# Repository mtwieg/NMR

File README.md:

NMR
===

Welcome to the Open Source Mobile NMR Relaxometry Platform repository on github.

You can download the entire repository without needing to install or register with github. To do so, go to the repository homepage and click the ZIP icon on the upper toolbar.

After presenting this project at ISMRM 2013, I received several questions about the future direction for the platform. At the moment there are numerous possible improvements to the hardware:

1. Further minitiarization (we estimate the platform could be shrunk by a factor of three or so without compromise).

2. Wider frequency range (for very low field work)

3. Addition of gradient amplifiers (imaging)

4. Greater processing power, for standalone data processing.

Such improvements should be driven by the intended applications of the platform, and at this time we have not settled on any applications to explore.  Until we decide what sort of applications are worth pursuing, we will probably hold off on any major hardware revisions.

We are, of course, open to any and all suggestions.

Mike Twieg
mdt24@case.edu

## Licensing

- content in `/BOMs` and `/EAGLE` is licensed under [CERN OHL P v2.0](LICENSES/CERN-OHL-P-2.0)
- content in `/BOMs` and `/EAGLE` is licensed under [MIT](LICENSES/MIT)
- content in `/BOMs` and `/EAGLE` is licensed under [CC BY 4.0](LICENSES/CC-BY-4.0)

See [.reuse/dep5](.reuse/dep5) for details.

Metadata is provided following the [REUSE specification v3.0](https://reuse.software/spec/)

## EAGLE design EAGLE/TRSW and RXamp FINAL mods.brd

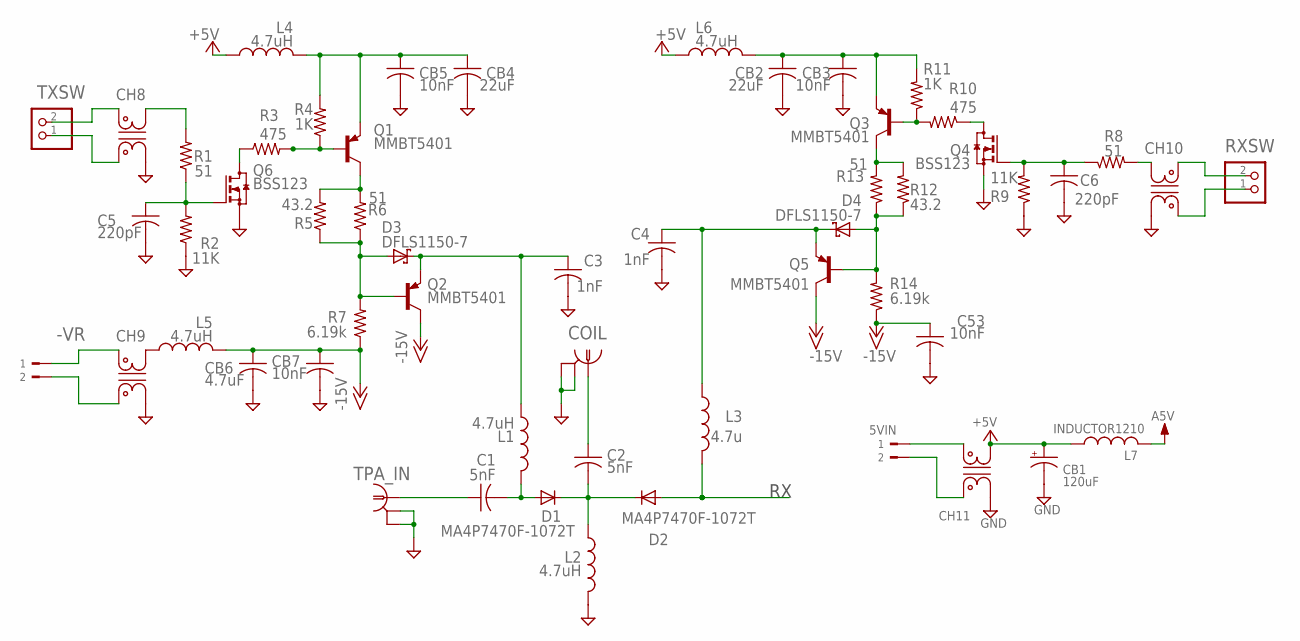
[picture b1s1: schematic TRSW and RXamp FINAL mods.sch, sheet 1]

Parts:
5VIN: TERM-2OMNIMATE_SL; OMNIMATE_SL_2POS
-VR: TERM-2OMNIMATE_SL; OMNIMATE_SL_2POS
C1, C2: 5nF; 1008
C3, C4: 1nF; C0805
C5, C6: 220pF; C0805
C53: 10nF; C0603
CB1: 120uF; E3,5-8
CB2, CB4: 22uF; C0805
CB3, CB5, CB7: 10nF; C0603
CB6: 4.7uF; C0805
CH8, CH10: CHOKEDLW31S; CHOKE_DLW31S
CH9, CH11: CHOKE; CHOKE_DLW5BT
COIL: BNC-EDGE
D1, D2: MA4P7470F-1072T; 1210-POLAR
D3, D4: DFLS1150-7; POWERDI-123
L1, L2, L4, L5, L6: 4.7uH; 1210
L3: 4.7u; 1210
L7: INDUCTOR1210; 1210
Q1, Q2, Q3, Q5: MMBT5401; SOT23-BEC
Q4, Q6: BSS123; SOT23
R1, R6, R8, R13: 51; R0805
R2, R9: 11K; R0805
R3, R10: 475; R0805
R4, R11: 1K; R0805
R5, R12: 43.2; R0805
R7, R14: 6.19k; R0805
RXSW: PINHD-1X2; 1X02
TPA_IN: BNC-EDGE
TXSW: PINHD-1X2; 1X02

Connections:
+5V: CB1.+, CH11.P$3 (3), L4.1, L6.2, L7.1
-15V: C53.1, CB6.1, CB7.1, L5.2, Q2.C, Q5.C, R7.1, R14.1
A5V: L7.2; also elsewhere on the board
GND: C3.2, C4.2, C5.2, C6.2, C53.2, CB1.-, CB2.2, CB3.2, CB4.2, CB5.2, CB6.2, CB7.2, CH8.P$2 (2), CH9.P$2 (2), CH10.P$2 (2), CH11.P$2 (2), COIL.S1 (GND1), COIL.S2 (GND2), L2.2, Q4.2 (S), Q6.2 (S), R2.1, R9.1, TPA_IN.S1 (GND1), TPA_IN.S2 (GND2); also elsewhere on the board
LNAIN: D2.A, L3.2; also elsewhere on the board
unnamed: D3.A, Q2.B, R5.1, R6.1, R7.2
unnamed: C3.1, D3.K (C), L1.1, Q2.E
unnamed: Q1.C, R5.2, R6.2
unnamed: Q1.B, R3.2, R4.1
unnamed: CH9.P$3 (3), L5.1
unnamed: C1.P$1 (1), TPA_IN.I (1)
unnamed: C1.P$2 (2), D1.A, L1.2
unnamed: C2.P$2 (2), D1.K (C), D2.K (C), L2.1
unnamed: CH8.P$3 (3), R1.2
unnamed: C2.P$1 (1), COIL.I (1)
unnamed: CH10.P$3 (3), R8.2
unnamed: CH10.P$4 (4), RXSW.2
unnamed: CH10.P$1 (1), RXSW.1
unnamed: CH8.P$4 (4), TXSW.2
unnamed: CH8.P$1 (1), TXSW.1
unnamed: 5VIN.1, CH11.P$4 (4)
unnamed: 5VIN.2, CH11.P$1 (1)
unnamed: -VR.1, CH9.P$4 (4)
unnamed: -VR.2, CH9.P$1 (1)
unnamed: D4.A, Q5.B, R12.1, R13.1, R14.2
unnamed: C4.1, D4.K (C), L3.1, Q5.E
unnamed: Q3.C, R12.2, R13.2
unnamed: Q3.B, R10.2, R11.1
unnamed: C6.1, Q4.1 (G), R8.1, R9.2
unnamed: Q6.3 (D), R3.1
unnamed: Q4.3 (D), R10.1
unnamed: C5.1, Q6.1 (G), R1.1, R2.2
unnamed: CB4.1, CB5.1, L4.2, Q1.E, R4.2
unnamed: CB2.1, CB3.1, L6.1, Q3.E, R11.2

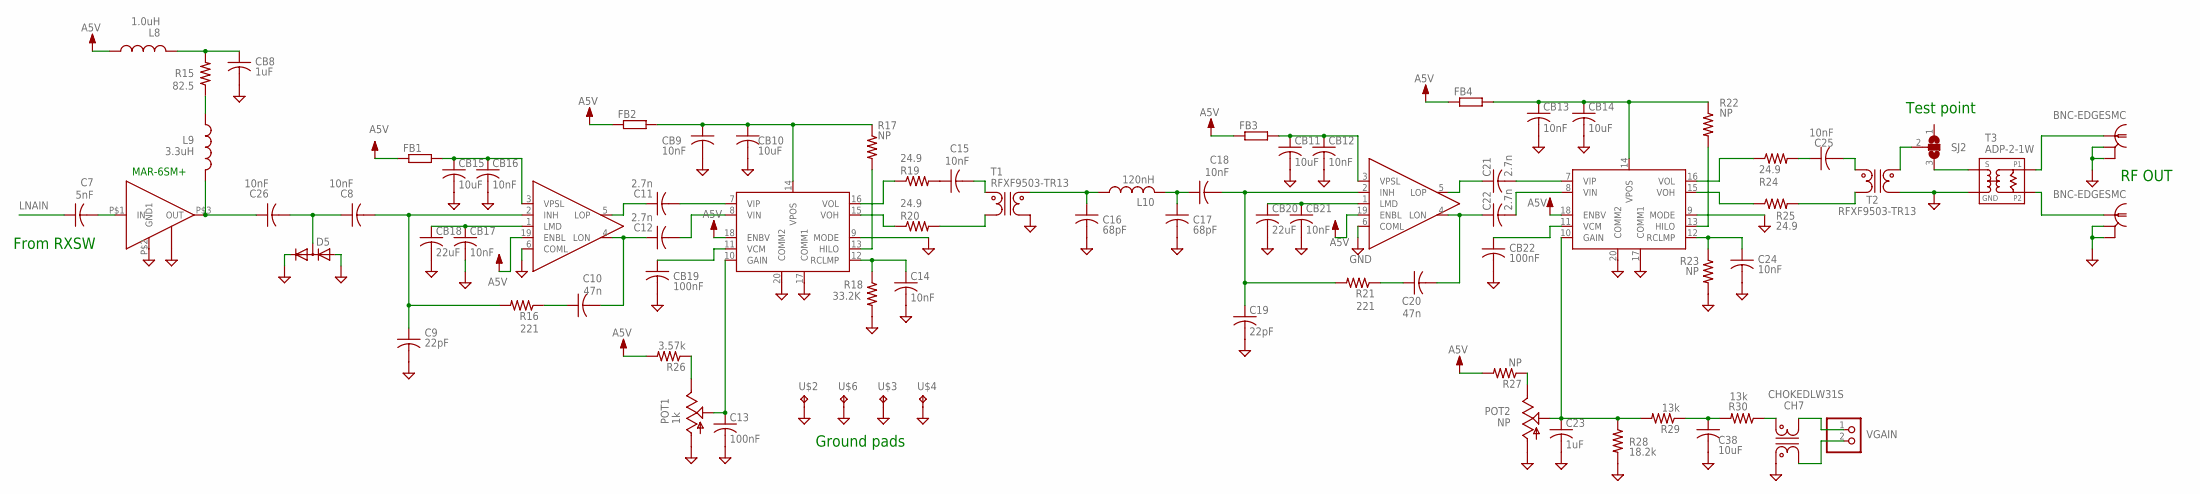
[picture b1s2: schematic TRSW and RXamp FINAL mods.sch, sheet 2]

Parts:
C7: 5nF; 1008
C8, C18, C26: 10nF; C0805
C9, C19: 22pF; C0805
C10, C20: 47n; C0805
C11, C12, C21, C22: 2.7n; C0603
C13: 100nF; C0603
C14, C15, C24, C25: 10nF; C0603
C16, C17: 68pF; 1008
C23: 1uF; C0805
C38: 10uF; C0805
CB8: 1uF; C0805
CB9, CB12, CB13, CB16, CB17, CB21: 10nF; C0603
CB10, CB11, CB14, CB15: 10uF; C0805
CB18, CB20: 22uF; C0805
CB19, CB22: 100nF; C0603
CH7: CHOKEDLW31S; CHOKE_DLW31S
D5: DIODE_2CACA-SOT23; SOT23
FB1, FB2, FB3, FB4: R-EU_R0603; R0603
L8: 1.0uH; 1008
L9: 3.3uH; 1008
L10: 120nH; 1008
LNA: MAR-6SM+; WW107
POT1: 1k; 3223W
POT2: NP; 3223W
R15: 82.5; R0805
R16, R21: 221; R0805
R17, R22, R23, R27: NP; R0805
R18: 33.2K; R0805
R19, R20, R24, R25: 24.9; R0805
R26: 3.57k; R0805
R28: 18.2k; R0805
R29, R30: 13k; R0805
RF_OUT: BNC-EDGESMC; SMC-EDGE
SJ2: SJ2W; SJ_2
T1, T2: RFXF9503-TR13; CX20XX_BALUN
T3: ADP-2-1W; CD636
U1, U2: AD8331; QSOP-20
U$2, U$3, U$4: TESTPOINTKEYSTONE_ELECTRONICS_5016; SMD_TESTPAD
U$6: SOLDERPADSMALL; PAD-SMALL
U$27: BNC-EDGESMC; SMC-EDGE
VGAIN: PINHD-1X2; 1X02

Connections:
A5V: FB1.1, FB2.1, FB3.1, FB4.1, L8.P$1 (1), R26.2, R27.2, U1.18 (ENBV), U1.19 (ENBL), U2.18 (ENBV), U2.19 (ENBL); also elsewhere on the board
GND: C9.2, C13.2, C14.2, C16.P$2 (2), C17.P$2 (2), C19.2, C23.2, C24.2, C38.2, CB8.2, CB9.2, CB10.2, CB11.2, CB12.2, CB13.2, CB14.2, CB15.2, CB16.2, CB17.2, CB18.2, CB19.2, CB20.2, CB21.2, CB22.2, CH7.P$1 (1), D5.1 (A), D5.2 (C), LNA.P$2 (GND1), LNA.P$4 (GND2), POT1.1 (A), POT2.1 (A), R18.2, R23.2, R28.2, RF_OUT.2 (GND1), RF_OUT.3 (GND2), T1.P$3 (3), T2.P$3 (3), T3.P$6 (GND), U1.6 (COML), U1.9 (MODE), U1.17 (COMM1), U1.20 (COMM2), U2.6 (COML), U2.9 (MODE), U2.17 (COMM1), U2.20 (COMM2), U$2.P$1, U$3.P$1, U$4.P$1, U$6.P$1, U$27.2 (GND1), U$27.3 (GND2); also elsewhere on the board
LNAIN: C7.P$1 (1); also elsewhere on the board
unnamed: C16.P$1 (1), L10.P$1 (1), T1.P$4 (4)
unnamed: C17.P$1 (1), C18.1, L10.P$2 (2)
unnamed: C8.2, C9.1, R16.2, U1.2 (INH)
unnamed: CH7.P$4 (4), R30.1
unnamed: CH7.P$3 (3), VGAIN.1
unnamed: CH7.P$2 (2), VGAIN.2
unnamed: C8.1, C26.2, D5.3 (AC)
unnamed: C26.1, L9.P$2 (2), LNA.P$3 (OUT)
unnamed: L9.P$1 (1), R15.1
unnamed: CB8.1, L8.P$2 (2), R15.2
unnamed: C7.P$2 (2), LNA.P$1 (IN)
unnamed: C11.1, U1.5 (LOP)
unnamed: C11.2, U1.7 (VIP)
unnamed: C12.2, U1.8 (VIN)
unnamed: C10.2, C12.1, U1.4 (LON)
unnamed: C15.1, R19.2
unnamed: C10.1, R16.1
unnamed: CB17.1, CB18.1, U1.1 (LMD)
unnamed: CB15.1, CB16.1, FB1.2, U1.3 (VPSL)
unnamed: CB19.1, U1.11 (VCM)
unnamed: R19.1, U1.16 (VOL)
unnamed: R20.1, U1.15 (VOH)
unnamed: C14.1, R18.1, U1.12 (RCLMP)
unnamed: CB9.1, CB10.1, FB2.2, R17.1, U1.14 (VPOS)
unnamed: R20.2, T1.P$1 (1)
unnamed: R17.2, U1.13 (HILO)
unnamed: C15.2, T1.P$5 (6)
unnamed: C13.1, POT1.2 (S), U1.10 (GAIN)
unnamed: POT1.3 (E), R26.1
unnamed: C18.2, C19.1, R21.2, U2.2 (INH)
unnamed: C21.1, U2.5 (LOP)
unnamed: C21.2, U2.7 (VIP)
unnamed: C22.2, U2.8 (VIN)
unnamed: C20.2, C22.1, U2.4 (LON)
unnamed: C20.1, R21.1
unnamed: CB20.1, CB21.1, U2.1 (LMD)
unnamed: CB11.1, CB12.1, FB3.2, U2.3 (VPSL)
unnamed: CB22.1, U2.11 (VCM)
unnamed: R24.1, U2.16 (VOL)
unnamed: R25.1, U2.15 (VOH)
unnamed: C24.1, R23.1, U2.12 (RCLMP)
unnamed: CB13.1, CB14.1, FB4.2, R22.1, U2.14 (VPOS)
unnamed: R22.2, U2.13 (HILO)
unnamed: C25.1, R24.2
unnamed: R25.2, T2.P$1 (1)
unnamed: C25.2, T2.P$5 (6)
unnamed: C23.1, POT2.2 (S), R28.1, R29.2, U2.10 (GAIN)
unnamed: POT2.3 (E), R27.1
unnamed: T3.P$4 (P2), U$27.1
unnamed: RF_OUT.1, T3.P$3 (P1)
unnamed: SJ2.2, T2.P$4 (4)
unnamed: SJ2.3, T3.P$1 (S)
RTY5: C38.1, R29.1, R30.2

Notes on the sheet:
Ground pads
Test point
RF OUT
From RXSW
MAR-6SM+

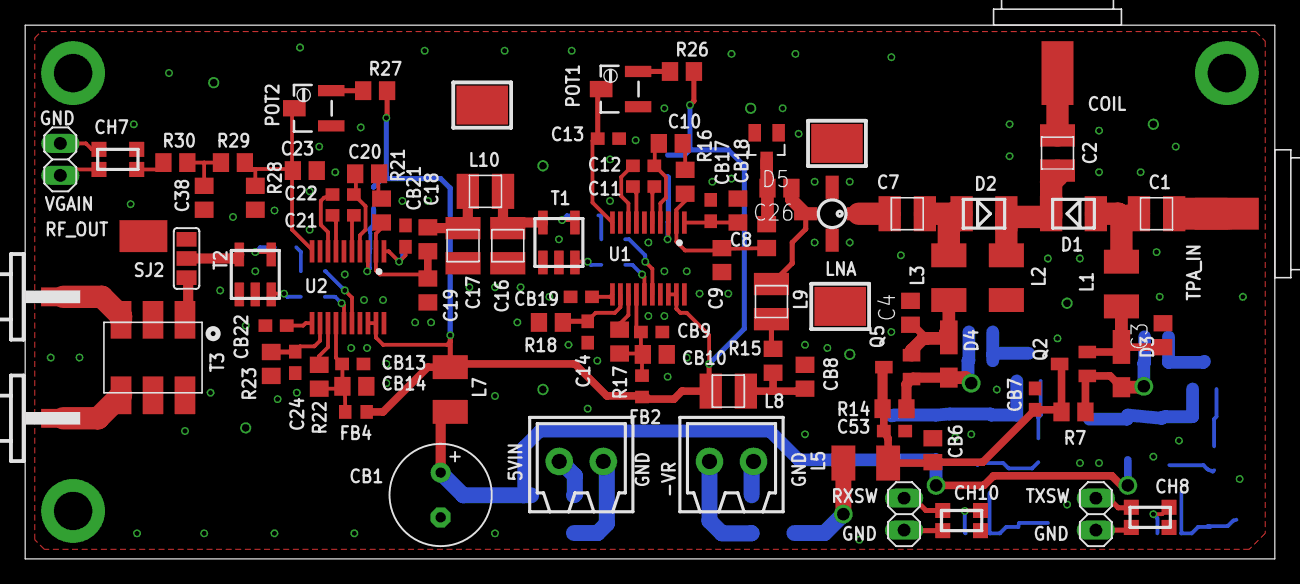
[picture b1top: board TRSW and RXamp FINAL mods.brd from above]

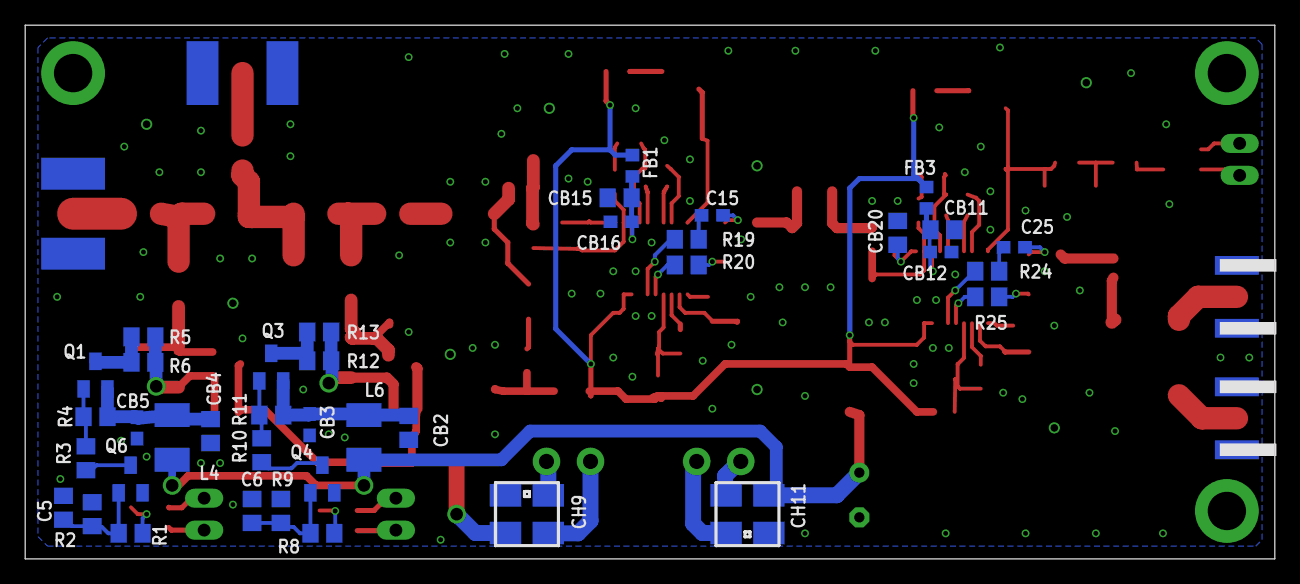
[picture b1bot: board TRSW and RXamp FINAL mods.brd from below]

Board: 4 copper layers, 99.3 x 42.4 mm, 132 parts (39 on the bottom side), 87 nets.

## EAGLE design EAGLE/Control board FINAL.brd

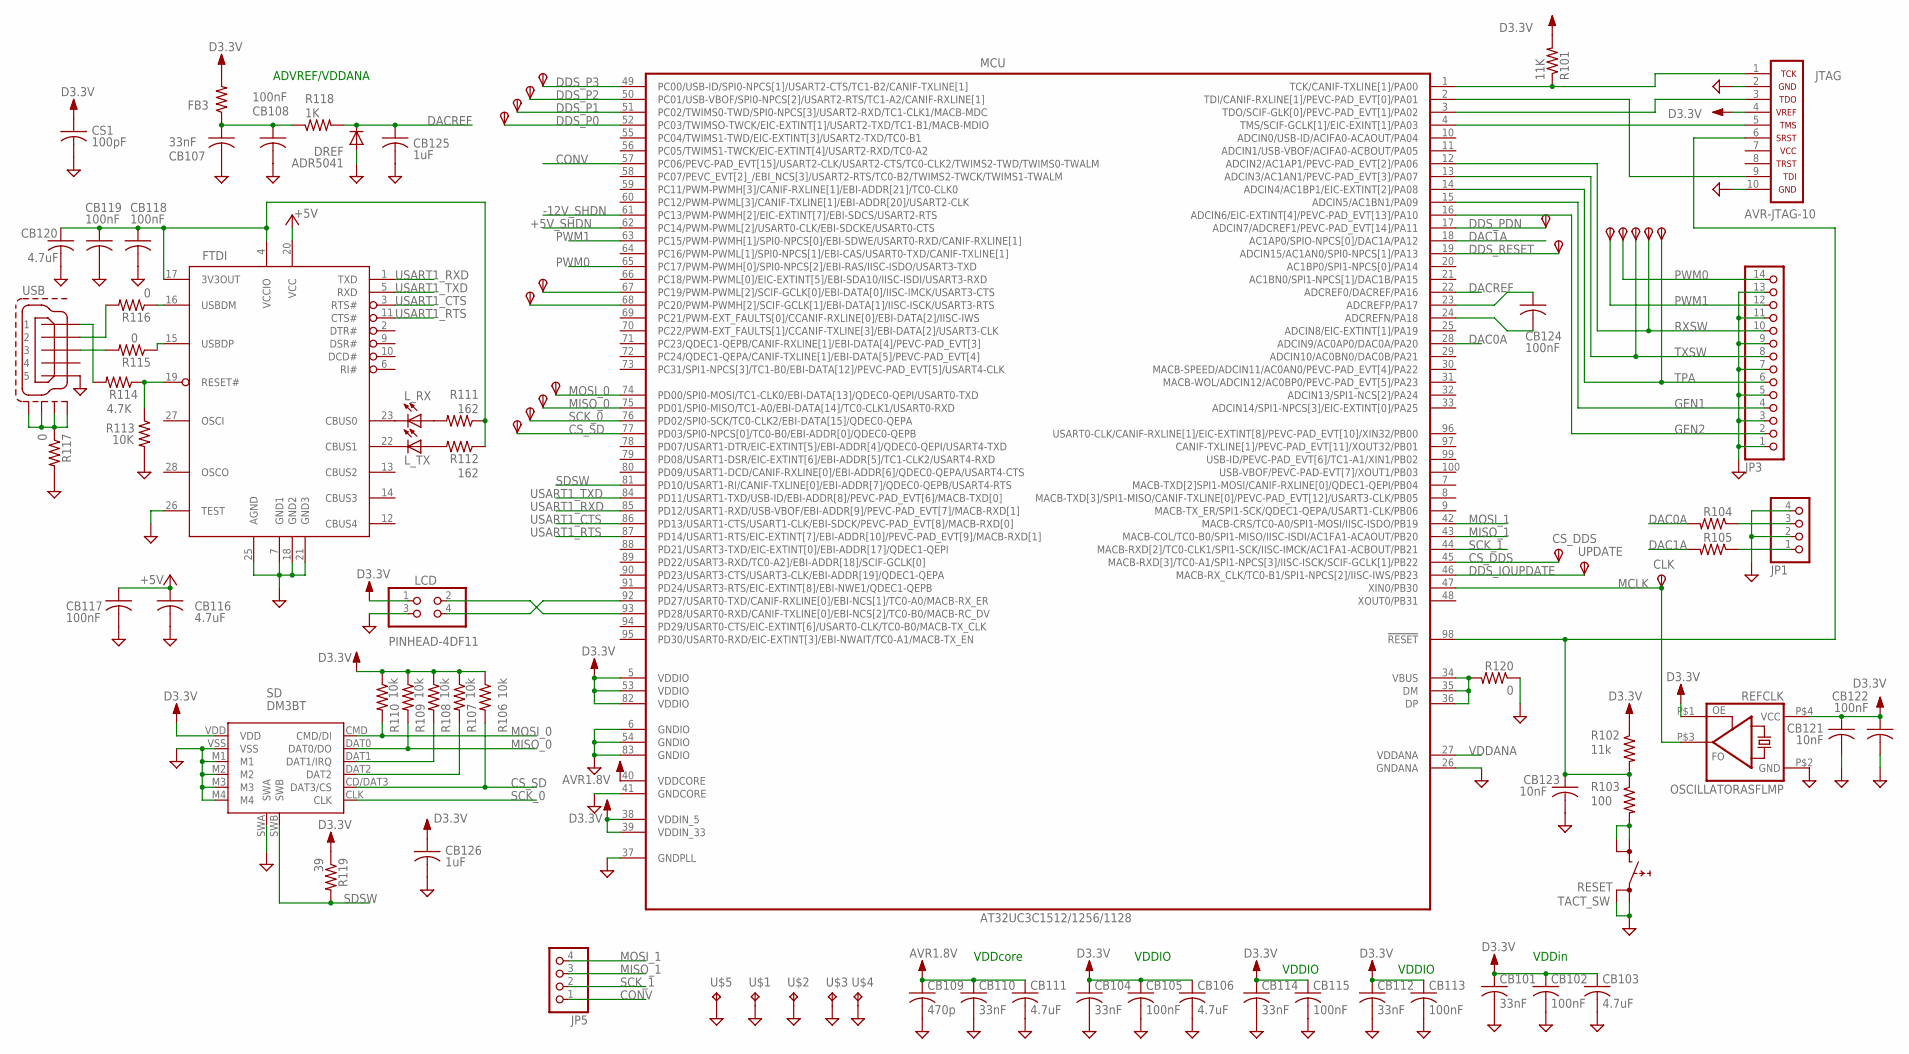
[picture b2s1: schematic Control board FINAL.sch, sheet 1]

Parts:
CB101, CB104, CB107, CB110, CB112, CB114: 33nF; C0603
CB102, CB105, CB108, CB113, CB115, CB117, CB118, CB119, CB122, CB124: 100nF; C0603
CB103, CB106, CB111, CB116, CB120: 4.7uF; C0805
CB109: 470p; C0603
CB121, CB123: 10nF; C0603
CB125, CB126: 1uF; C0603
CLK: TPSTP10R; TP10R
CS1: 100pF; C0805
CS_DDS: TPSTP10R; TP10R
CS_SD: TPSTP10R; TP10R
DDSPDN: TPSTP10R; TP10R
DDSRESET: TPSTP10R; TP10R
DREF: ADR5041; SOT23-3
FB3: R-US_R0603; R0603
FTDI: FT232RL; SSOP28DB
GCLK0, GCLK1: TPSTP10R; TP10R
JP1, JP5: PINHD-1X4; 1X04
JP3: PINHD-1X14; 1X14
JTAG: AVR-JTAG-10
LCD: PINHEAD-4DF11; DF11-4POS
L_RX: LEDCHIPLED_0805; CHIPLED_0805
L_TX: LEDCHIPLED_0805; CHIPLED_0805
MCU: AT32UC3C1512/1256/1128; TQFP100
MISO0: TPSTP10R; TP10R
MOSI0: TPSTP10R; TP10R
P0, P1, P2, P3: TPSTP10R; TP10R
R101: 11K; R0805
R102: 11k; R0805
R103: 100; R0805
R104, R105: R-US_R0805; R0805
R106, R107, R108, R109, R110: 10k; R0805
R111, R112: 162; R0805
R113: 10K; R0805
R114: 4.7K; R0805
R115, R116, R117, R120: 0; R0805
R118: 1K; R0805
R119: 39; R0805
REFCLK: OSCILLATORASFLMP; QFN4_ASFLMP_OSCILLATOR
RESET: TACT_SW; KMR2_TACT_SWITCH
SCK0: TPSTP10R; TP10R
SD: DM3BT
TP1, TP2, TP3, TP4, TP5: TPSTP10R; TP10R
U$1, U$2, U$3, U$4, U$5: TESTPOINTKEYSTONE_ELECTRONICS_5016; SMD_TESTPAD
UPDATE: TPSTP10R; TP10R
USB: MINI-USB-SHIELD-UX60A-MB-5ST; UX60A-MB-5ST

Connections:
+5V: CB116.1, CB117.1, FTDI.20 (VCC); also elsewhere on the board
+5V_SHDN: MCU.62 (PC14/PWM-PWML[2]/USART0-CLK/EBI-SDCKE/U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); also elsewhere on the board
-12V_SHDN: MCU.61 (PC13/PWM-PWMH[2]/EIC-EXTINT[7]/EBI-SDCS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); also elsewhere on the board
AVR1.8V: CB109.1, CB110.1, CB111.1, MCU.40 (VDDCORE)
CONV: JP5.1, MCU.57 (PC06/PEVC-PAD_EVT[15]/USART2-CLK/USART2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); also elsewhere on the board
CS_DDS: CS_DDS.TP, MCU.45 (MACB-RXD[3]/TC0-A1/SPI1-NPCS[3]/IISC-IS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); also elsewhere on the board
CS_SD: CS_SD.TP, MCU.77 (PD03/SPI0-NPCS[0]/TC0-B0/EBI-ADDR[0]/QD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), R106.2, SD.CD/DAT3 (DAT3/CS)
D3.3V: CB101.1, CB102.1, CB103.1, CB104.1, CB105.1, CB106.1, CB112.1, CB113.1, CB114.1, CB115.1, CB121.1, CB122.1, CB126.1, CS1.1, FB3.2, JTAG.4, LCD.1, MCU.5 (VDDIO), MCU.38 (VDDIN_5), MCU.39 (VDDIN_33), MCU.53 (VDDIO), MCU.82 (VDDIO), R101.2, R102.1, R106.1, R107.1, R108.1, R109.1, R110.1, R119.1, REFCLK.P$1 (OE), REFCLK.P$4 (VCC), SD.VDD; also elsewhere on the board
DAC0A: MCU.28 (ADCIN9/AC0AP0/DAC0A/PA20), R104.2
DAC1A: MCU.18 (AC1AP0/SPIO-NPCS[0]/DAC1A/PA12), R105.2
DACREF: CB125.1, DREF.1 (C), MCU.22 (ADCREF0/DACREF/PA16), R118.2
DDS_IOUPDATE: MCU.46 (MACB-RX_CLK/TC0-B1/SPI1-NPCS[2]/IISC-IW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), UPDATE.TP; also elsewhere on the board
DDS_P0: MCU.52 (PC03/TWIMSO-TWCK/EIC-EXTINT[1]/USART2-T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), P0.TP; also elsewhere on the board
DDS_P1: MCU.51 (PC02/TWIMS0-TWD/SPI0-NPCS[3]/USART2-RXD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), P1.TP; also elsewhere on the board
DDS_P2: MCU.50 (PC01/USB-VBOF/SPI0-NPCS[2]/USART2-RTS/T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), P2.TP; also elsewhere on the board
DDS_P3: MCU.49 (PC00/USB-ID/SPI0-NPCS[1]/USART2-CTS/TC1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), P3.TP; also elsewhere on the board
DDS_PDN: DDSPDN.TP, MCU.17 (ADCIN7/ADCREF1/PEVC-PAD_EVT[14]/PA11); also elsewhere on the board
DDS_RESET: DDSRESET.TP, MCU.19 (ADCIN15/AC1AN0/SPI0-NPCS[1]/PA13); also elsewhere on the board
DGND: USB.5
GEN1: JP3.4, MCU.15 (ADCIN5/AC1BN1/PA09)
GEN2: JP3.2, MCU.16 (ADCIN6/EIC-EXTINT[4]/PEVC-PAD_EVT[13]/P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)
GND: CB101.2, CB102.2, CB103.2, CB104.2, CB105.2, CB106.2, CB107.2, CB108.2, CB109.2, CB110.2, CB111.2, CB112.2, CB113.2, CB114.2, CB115.2, CB116.2, CB117.2, CB118.2, CB119.2, CB120.2, CB121.2, CB122.2, CB123.2, CB125.2, CB126.2, CS1.2, DREF.2 (A), FTDI.7 (GND1), FTDI.18 (GND2), FTDI.21 (GND3), FTDI.25 (AGND), FTDI.26 (TEST), JP1.2, JP1.4, JP3.1, JP3.3, JP3.5, JP3.7, JP3.9, JP3.11, JP3.13, JTAG.2, JTAG.10, LCD.3, MCU.6 (GNDIO), MCU.26 (GNDANA), MCU.37 (GNDPLL), MCU.41 (GNDCORE), MCU.54 (GNDIO), MCU.83 (GNDIO), R113.2, R117.2, R120.1, REFCLK.P$2 (GND), RESET.P$1 (0), RESET.P$3 (0), SD.M1, SD.M2, SD.M3, SD.M4, SD.SWA, SD.VSS, U$1.P$1, U$2.P$1, U$3.P$1, U$4.P$1, U$5.P$1; also elsewhere on the board
MCLK: CLK.TP, MCU.47 (XIN0/PB30), REFCLK.P$3 (FO); also elsewhere on the board
MISO_0: MCU.75 (PD01/SPI0-MISO/TC1-A0/EBI-DATA[14]/TC0-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), MISO0.TP, R109.2, SD.DAT0 (DAT0/DO)
MISO_1: JP5.3, MCU.43 (MACB-COL/TC0-B0/SPI1-MISO/IISC-ISDI/AC1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); also elsewhere on the board
MOSI_0: MCU.74 (PD00/SPI0-MOSI/TC1-CLK0/EBI-DATA[13]/QD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), MOSI0.TP, R110.2, SD.CMD (CMD/DI)
MOSI_1: JP5.4, MCU.42 (MACB-CRS/TC0-A0/SPI1-MOSI/IISC-ISDO/PB19); also elsewhere on the board
unnamed: CB123.1, JTAG.6, MCU.98 (!RESET), R102.2, R103.1
unnamed: JTAG.1, MCU.1 (TCK/CANIF-TXLINE[1]/PA00), R101.1
unnamed: JTAG.9, MCU.2 (TDI/CANIF-RXLINE[1]/PEVC-PAD_EVT[0]/PA01)
unnamed: JTAG.3, MCU.3 (TDO/SCIF-GLK[0]/PEVC-PAD_EVT[1]/PA02)
unnamed: JTAG.5, MCU.4 (TMS/SCIF-GCLK[1]/EIC-EXINT[1]/PA03)
unnamed: JP1.3, R104.1
unnamed: CB118.1, CB119.1, CB120.1, FTDI.4 (VCCIO), FTDI.17 (3V3OUT), R111.1, R112.1
unnamed: R115.2, USB.3
unnamed: R116.2, USB.2
unnamed: FTDI.15 (USBDP), R115.1
unnamed: FTDI.16 (USBDM), R116.1
unnamed: FTDI.19 (RESET#), R113.1, R114.1
unnamed: R114.2, USB.1
unnamed: CB124.2, MCU.24 (ADCREFN/PA18)
unnamed: R103.2, RESET.P$2 (1), RESET.P$4 (1)
unnamed: R108.2, SD.DAT1 (DAT1/IRQ)
unnamed: R107.2, SD.DAT2
unnamed: CB124.1, MCU.23 (ADCREFP/PA17)
unnamed: JP1.1, R105.1
unnamed: R117.1, USB.M1 (S1), USB.M2 (S2), USB.M3 (S3), USB.M4 (S4)
unnamed: MCU.34 (VBUS), MCU.35 (DM), MCU.36 (DP), R120.2
unnamed: FTDI.23 (CBUS0), L_RX.C
unnamed: L_RX.A, R111.2
unnamed: L_TX.A, R112.2
unnamed: FTDI.22 (CBUS1), L_TX.C
unnamed: GCLK0.TP, MCU.67 (PC19/PWM-PWML[2]/SCIF-GCLK[0]/EBI-DATA[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)
unnamed: GCLK1.TP, MCU.68 (PC20/PWM-PWMH[2]/SCIF-GCLK[1]/EBI-DATA[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)
PWM0: JP3.14, MCU.65 (PC17/PWM-PWMH[0]/SPI0-NPCS[2]/EBI-RAS/I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), TP2.TP
PWM1: JP3.12, MCU.63 (PC15/PWM-PWMH[1]/SPI0-NPCS[0]/EBI-SDWE/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), TP1.TP
RXSW: JP3.10, MCU.12 (ADCIN2/AC1AP1/PEVC-PAD_EVT[2]/PA06), TP4.TP
SCK_0: MCU.76 (PD02/SPI0-SCK/TC0-CLK2/EBI-DATA[15]/QDE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), SCK0.TP, SD.CLK
SCK_1: JP5.2, MCU.44 (MACB-RXD[2]/TC0-CLK1/SPI1-SCK/IISC-IMCK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); also elsewhere on the board
SDSW: MCU.81 (PD10/USART1-RI/CANIF-TXLINE[0]/EBI-ADDR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), R119.2, SD.SWB
TPA: JP3.6, MCU.14 (ADCIN4/AC1BP1/EIC-EXTINT[2]/PA08), TP5.TP
TXSW: JP3.8, MCU.13 (ADCIN3/AC1AN1/PEVC-PAD_EVT[3]/PA07), TP3.TP
USART0_RXD: LCD.2, MCU.93 (PD28/USART0-RXD/CANIF-TXLINE[0]/EBI-NCS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)
USART0_TXD: LCD.4, MCU.92 (PD27/USART0-TXD/CANIF-RXLINE[0]/EBI-NCS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)
USART1_CTS: FTDI.3 (RTS#), MCU.86 (PD13/USART1-CTS/USART1-CLK/EBI-SDCK/PEV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)
USART1_RTS: FTDI.11 (CTS#), MCU.87 (PD14/USART1-RTS/EIC-EXTINT[7]/EBI-ADDR[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)
USART1_RXD: FTDI.1 (TXD), MCU.85 (PD12/USART1-RXD/USB-VBOF/EBI-ADDR[9]/PE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)
USART1_TXD: FTDI.5 (RXD), MCU.84 (PD11/USART1-TXD/USB-ID/EBI-ADDR[8]/PEVC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)
VDDANA: CB107.1, CB108.1, FB3.1, MCU.27 (VDDANA), R118.1

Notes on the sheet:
VDDcore
VDDin
VDDIO
ADVREF/VDDANA

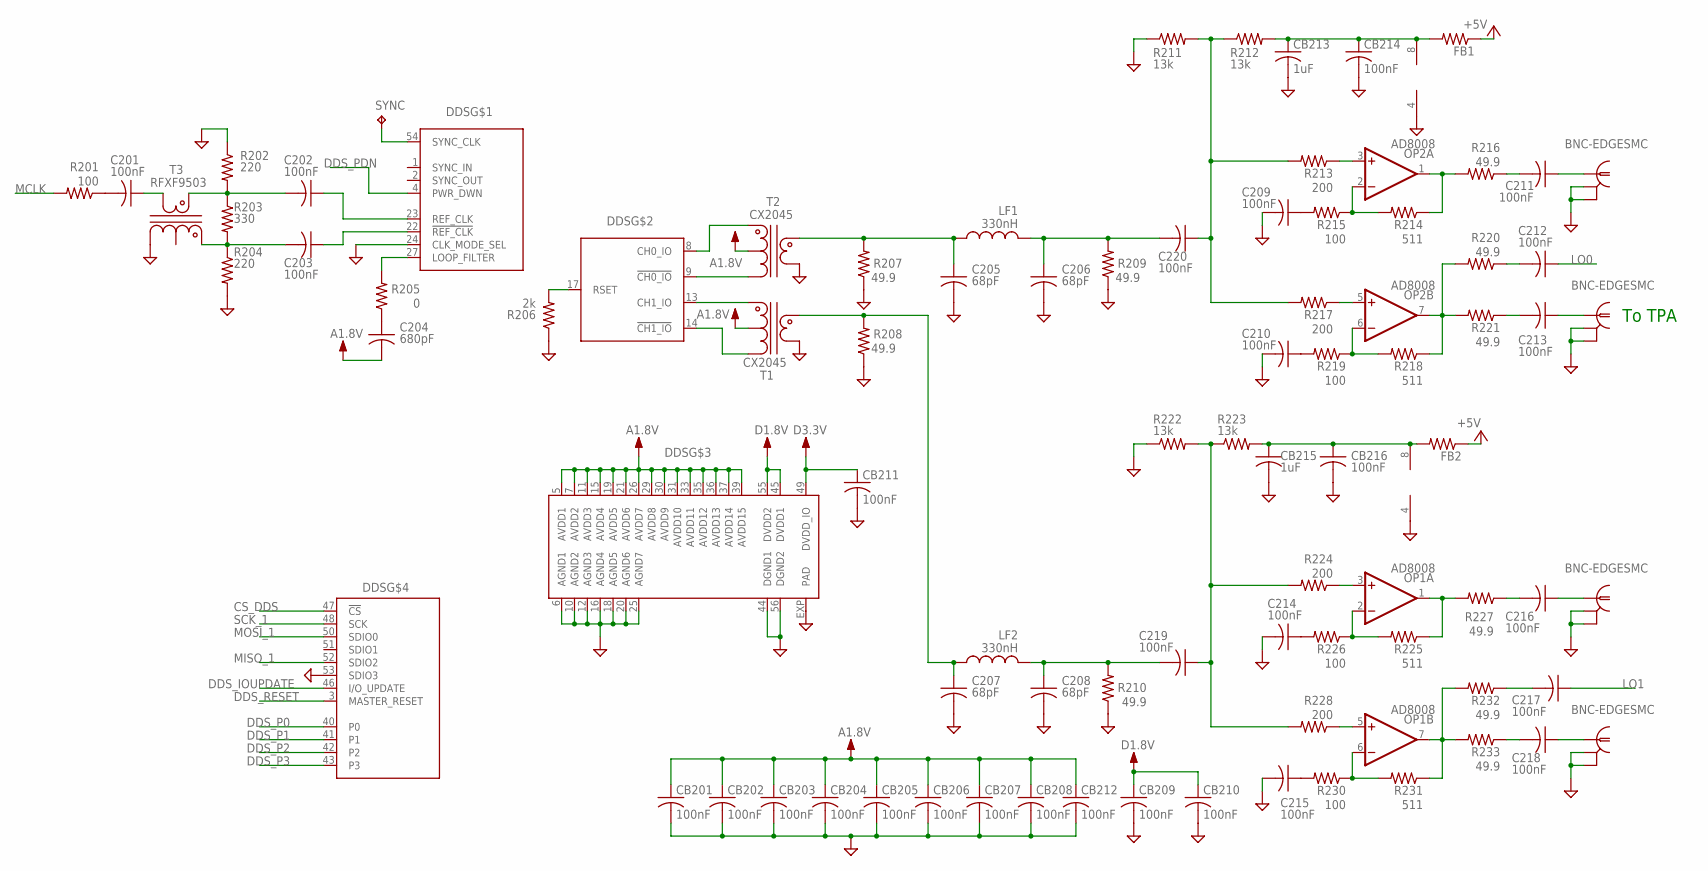
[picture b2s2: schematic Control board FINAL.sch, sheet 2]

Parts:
C201, C202, C203, C209, C210, C211, C212, C213, C214, C215, C216, C217, C218, C219, C220: 100nF; C0603
C204: 680pF; C0805
C205, C206, C207, C208: 68pF; 1008
CB201, CB202, CB203, CB204, CB205, CB206, CB207, CB208, CB209, CB210, CB211, CB212, CB214, CB216: 100nF; C0603
CB213, CB215: 1uF; C0805
DDS: AD9958; LFCSP-56
FB1, FB2: R-US_R0603; R0603
LF1, LF2: 330nH; 1008
LO0, LO1: BNC-EDGESMC; SMC-EDGE
OP1, OP2: AD8008; SO08
R201, R215, R219, R226, R230: 100; R0805
R202, R204: 220; R0805
R203: 330; R0805
R205: 0; R0805
R206: 2k; R0805
R207, R208, R209, R210, R216, R220, R221, R227, R232, R233: 49.9; R0805
R211, R212, R222, R223: 13k; R0805
R213, R217, R224, R228: 200; R0805
R214, R218, R225, R231: 511; R0805
SYNC: TPTP10R; TP10R
T1, T2: CX2045; CX20XX_BALUN
T3: RFXF9503; CX20XX_BALUN
TX0, TX1: BNC-EDGESMC; SMC-EDGE

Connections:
+5V: FB1.1, FB2.1; also elsewhere on the board
A1.8V: C204.2, CB201.1, CB202.1, CB203.1, CB204.1, CB205.1, CB206.1, CB207.1, CB208.1, CB212.1, DDS.5 (AVDD1), DDS.7 (AVDD2), DDS.11 (AVDD3), DDS.15 (AVDD4), DDS.19 (AVDD5), DDS.21 (AVDD6), DDS.26 (AVDD7), DDS.29 (AVDD8), DDS.30 (AVDD9), DDS.31 (AVDD10), DDS.33 (AVDD11), DDS.35 (AVDD12), DDS.36 (AVDD13), DDS.37 (AVDD14), DDS.39 (AVDD15), T1.P$2 (5), T2.P$2 (5); also elsewhere on the board
A12V1: CB213.1, CB214.1, FB1.2, OP2.8 (V+), R212.2
A12V2: CB215.1, CB216.1, FB2.2, OP1.8 (V+), R223.2
C201: C201.2, R201.1
CS_DDS: DDS.47 (!CS); also elsewhere on the board
D1.8V: CB209.1, CB210.1, DDS.45 (DVDD1), DDS.55 (DVDD2); also elsewhere on the board
D3.3V: CB211.1, DDS.49 (DVDD_IO); also elsewhere on the board
DDS_IOUPDATE: DDS.46 (I/O_UPDATE); also elsewhere on the board
DDS_P0: DDS.40 (P0); also elsewhere on the board
DDS_P1: DDS.41 (P1); also elsewhere on the board
DDS_P2: DDS.42 (P2); also elsewhere on the board
DDS_P3: DDS.43 (P3); also elsewhere on the board
DDS_PDN: DDS.4 (PWR_DWN); also elsewhere on the board
DDS_RESET: DDS.3 (MASTER_RESET); also elsewhere on the board
GND: C205.P$2 (2), C206.P$2 (2), C207.P$2 (2), C208.P$2 (2), C209.2, C210.2, C214.2, C215.2, CB201.2, CB202.2, CB203.2, CB204.2, CB205.2, CB206.2, CB207.2, CB208.2, CB209.2, CB210.2, CB211.2, CB212.2, CB213.2, CB214.2, CB215.2, CB216.2, DDS.6 (AGND1), DDS.10 (AGND2), DDS.12 (AGND3), DDS.16 (AGND4), DDS.18 (AGND5), DDS.20 (AGND6), DDS.24 (CLK_MODE_SEL), DDS.25 (AGND7), DDS.44 (DGND1), DDS.53 (SDIO3), DDS.56 (DGND2), DDS.EXP (PAD), LO0.2 (GND1), LO0.3 (GND2), LO1.2 (GND1), LO1.3 (GND2), OP1.4 (V-), OP2.4 (V-), R202.1, R204.2, R206.1, R207.1, R208.1, R209.1, R210.1, R211.1, R222.1, T1.P$4 (3), T2.P$4 (3), T3.P$3 (4), TX0.2 (GND1), TX0.3 (GND2), TX1.2 (GND1), TX1.3 (GND2); also elsewhere on the board
LO0: C212.1; also elsewhere on the board
LO1: C217.1; also elsewhere on the board
MCLK: R201.2; also elsewhere on the board
MISO_1: DDS.52 (SDIO2); also elsewhere on the board
MOSI_1: DDS.50 (SDIO0); also elsewhere on the board
unnamed: C212.2, R220.1
unnamed: DDS.9 (!CH0_IO), T2.P$3 (4)
unnamed: DDS.8 (CH0_IO), T2.P$1 (6)
unnamed: DDS.14 (!CH1_IO), T1.P$3 (4)
unnamed: DDS.13 (CH1_IO), T1.P$1 (6)
unnamed: C202.1, DDS.23 (REF_CLK)
unnamed: C203.1, DDS.22 (!REF_CLK)
unnamed: C202.2, R202.2, R203.1, T3.P$5 (1)
unnamed: C204.1, R205.1
unnamed: DDS.27 (LOOP_FILTER), R205.2
unnamed: C203.2, R203.2, R204.1, T3.P$1 (6)
unnamed: DDS.17 (RSET), R206.2
unnamed: C217.2, R232.1
unnamed: DDS.54 (SYNC_CLK), SYNC.TP
unnamed: C207.P$1 (1), LF2.P$1 (1), R208.2, T1.P$5 (1)
unnamed: C205.P$1 (1), LF1.P$1 (1), R207.2, T2.P$5 (1)
unnamed: C206.P$1 (1), C220.2, LF1.P$2 (2), R209.2
unnamed: C209.1, R215.2
unnamed: OP2.2 (-IN), R214.2, R215.1
unnamed: OP2.1 (OUT), R214.1, R216.2
unnamed: OP2.3 (+IN), R213.1
unnamed: OP2.6 (-IN), R218.2, R219.1
unnamed: OP2.7 (OUT), R218.1, R220.2, R221.2
unnamed: OP2.5 (+IN), R217.1
unnamed: C210.1, R219.2
unnamed: C208.P$1 (1), C219.2, LF2.P$2 (2), R210.2
unnamed: C211.1, TX0.1
unnamed: C214.1, R226.2
unnamed: OP1.2 (-IN), R225.2, R226.1
unnamed: OP1.1 (OUT), R225.1, R227.2
unnamed: OP1.3 (+IN), R224.1
unnamed: OP1.6 (-IN), R230.1, R231.2
unnamed: OP1.7 (OUT), R231.1, R232.2, R233.2
unnamed: OP1.5 (+IN), R228.1
unnamed: C215.1, R230.2
unnamed: C219.1, R222.2, R223.1, R224.2, R228.2
unnamed: C211.2, R216.1
unnamed: C213.1, LO0.1
unnamed: C213.2, R221.1
unnamed: C216.1, TX1.1
unnamed: C216.2, R227.1
unnamed: C218.1, LO1.1
unnamed: C218.2, R233.1
unnamed: C201.1, T3.P$4 (3)
R211: C220.1, R211.2, R212.1, R213.2, R217.2
SCK_1: DDS.48 (SCK); also elsewhere on the board

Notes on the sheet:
To TPA

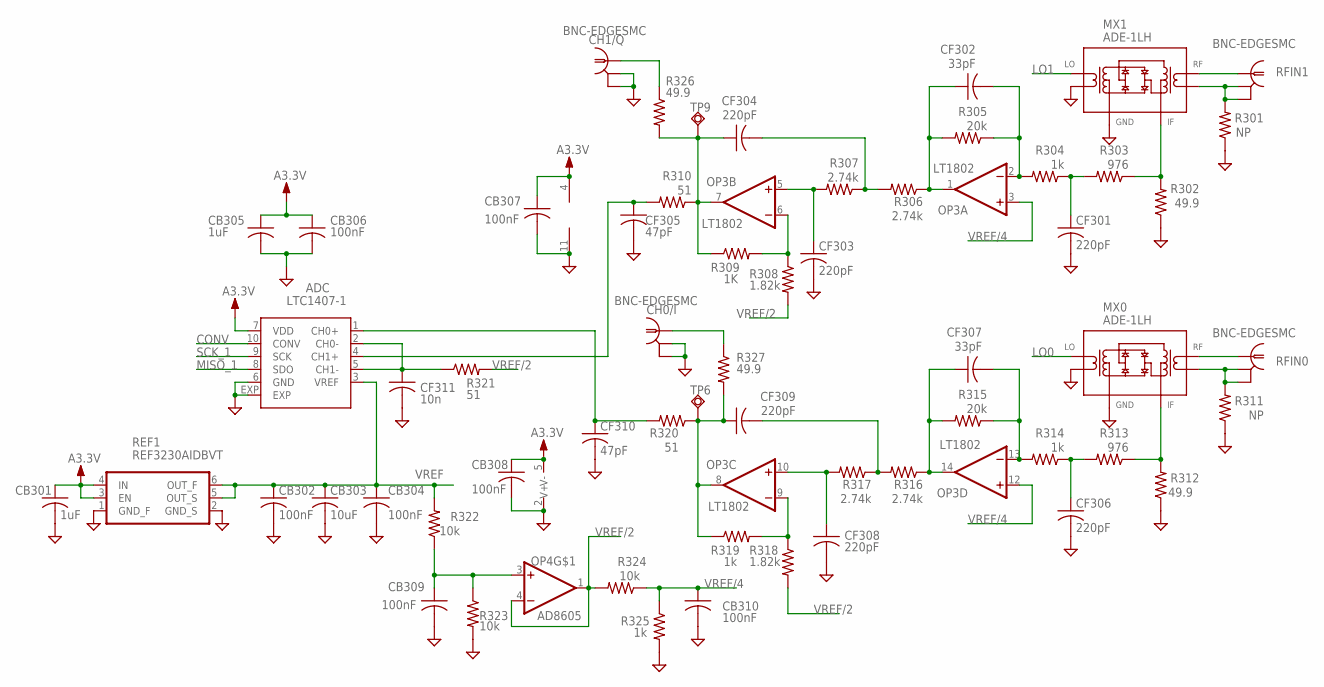
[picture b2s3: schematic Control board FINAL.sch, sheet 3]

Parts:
ADC: LTC1407-1; MSOP-10-EXP
CB301, CB305: 1uF; C0603
CB302, CB304, CB306, CB307, CB308, CB309, CB310: 100nF; C0603
CB303: 10uF; C0805
CF301, CF303, CF304, CF306, CF308, CF309: 220pF; C0805
CF302, CF307: 33pF; C0805
CF305, CF310: 47pF; C0603
CF311: 10n; C0603
CH0/I, CH1/Q: BNC-EDGESMC; SMC-EDGE
MX0, MX1: ADE-1LH; CD636
OP3: LT1802; SO14
OP4: AD8605; SOT23-5
R301, R311: NP; R0805
R302, R312, R326, R327: 49.9; R0805
R303, R313: 976; R0805
R304, R314, R319, R325: 1k; R0805
R305, R315: 20k; R0805
R306, R307, R316, R317: 2.74k; R0805
R308, R318: 1.82k; R0805
R309: 1K; R0805
R310, R320, R321: 51; R0805
R322, R323, R324: 10k; R0805
REF1: REF3230AIDBVT; SOT23-6
RFIN0, RFIN1: BNC-EDGESMC; SMC-EDGE
TP6, TP9: TPSQTP16R; TP16R

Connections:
A3.3V: ADC.7 (VDD), CB301.1, CB305.1, CB306.1, CB307.1, CB308.1, OP3.4 (V+), OP4.5 (V+), REF1.3 (EN), REF1.4 (IN); also elsewhere on the board
CONV: ADC.10 (CONV); also elsewhere on the board
GND: ADC.6 (GND), ADC.EXP, CB301.2, CB302.2, CB303.2, CB304.2, CB305.2, CB306.2, CB307.2, CB308.2, CB309.2, CB310.2, CF301.2, CF303.2, CF305.2, CF306.2, CF308.2, CF310.2, CF311.2, CH0/I.2 (GND1), CH0/I.3 (GND2), CH1/Q.2 (GND1), CH1/Q.3 (GND2), MX0.P$1 (LON), MX0.P$5 (GND), MX1.P$1 (LON), MX1.P$5 (GND), OP3.11 (V-), OP4.2 (V-), R301.1, R302.1, R311.1, R312.1, R323.2, R325.2, REF1.1 (GND_F), REF1.2 (GND_S); also elsewhere on the board
LO0: MX0.P$6 (LOP); also elsewhere on the board
LO1: MX1.P$6 (LOP); also elsewhere on the board
MISO_1: ADC.8 (SDO); also elsewhere on the board
unnamed: CH0/I.1, R327.1
unnamed: CH1/Q.1, R326.1
unnamed: CF307.2, OP3.13 (-IN), R314.2, R315.1
unnamed: CF309.2, R316.2, R317.1
unnamed: CF308.1, OP3.10 (+IN), R317.2
unnamed: OP3.9 (-IN), R318.1, R319.2
unnamed: ADC.4 (CH1+), CF305.1, R310.2
unnamed: CF307.1, OP3.14 (OUT), R315.2, R316.1
unnamed: CF306.1, R313.2, R314.1
unnamed: MX0.P$2 (IF), R312.2, R313.1
unnamed: CF302.2, OP3.2 (-IN), R304.2, R305.1
unnamed: CF304.2, R306.2, R307.1
unnamed: CF303.1, OP3.5 (+IN), R307.2
unnamed: OP3.6 (-IN), R308.1, R309.2
unnamed: CF304.1, OP3.7 (OUT), R309.1, R310.1, R326.2, TP9.TP
unnamed: CF302.1, OP3.1 (OUT), R305.2, R306.1
unnamed: CF301.1, R303.2, R304.1
unnamed: MX1.P$2 (IF), R302.2, R303.1
unnamed: MX1.P$3 (RFP), RFIN1.1
unnamed: MX0.P$3 (RFP), RFIN0.1
unnamed: ADC.2 (CH0-), ADC.5 (CH1-), CF311.1, R321.1
unnamed: CB309.1, OP4.3 (+IN), R322.1, R323.1
unnamed: CF309.1, OP3.8 (OUT), R319.1, R320.1, R327.2, TP6.TP
unnamed: ADC.1 (CH0+), CF310.1, R320.2
unnamed: MX0.P$4 (RFN), R311.2, RFIN0.2 (GND1), RFIN0.3 (GND2)
unnamed: MX1.P$4 (RFN), R301.2, RFIN1.2 (GND1), RFIN1.3 (GND2)
SCK_1: ADC.9 (SCK); also elsewhere on the board
VREF: ADC.3 (VREF), CB302.1, CB303.1, CB304.1, R322.2, REF1.5 (OUT_S), REF1.6 (OUT_F)
VREF/2: OP4.1 (OUT), OP4.4 (-IN), R308.2, R318.2, R321.2, R324.2
VREF/4: CB310.1, OP3.3 (+IN), OP3.12 (+IN), R324.1, R325.1
